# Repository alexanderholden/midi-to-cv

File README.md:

# MIDI to CV converter
This is a project that will allow me to read MIDI commands from my computer and then play my analogue synthesisers with it.

This is the first version and it features a 1V/Oct output and a gate output.

## Future upgrades:
- More features (CC and velocity for example)
- Upgrade to USB-C
- Redesign PCB to be more efficient and not require an entire Raspberry Pi Pico

## Current status:
- PCB ordered
- Custom firmware in development

## Rendering:

## Schematic:

## Parts list:

- Raspberry Pi Pico 2020
- MCP4725 12-bit DAC
- 2x 2K resistors
- 3x 10K resistors
- Polulu 5V step up converter
- 2x 1/4 audio jack

## Sources:

- MCP4725 breakout board schematic: https://learn.adafruit.com/mcp4725-12-bit-dac-tutorial/download
- QtPy MIDI to CV Skull: https://learn.adafruit.com/circuitpython-midi-to-cv-skull
- MIDI info: https://www.instructables.com/Send-and-Receive-MIDI-with-Arduino/
- Arduino MIDI to CV: https://www.instructables.com/Another-MIDI-to-CV-Box-/

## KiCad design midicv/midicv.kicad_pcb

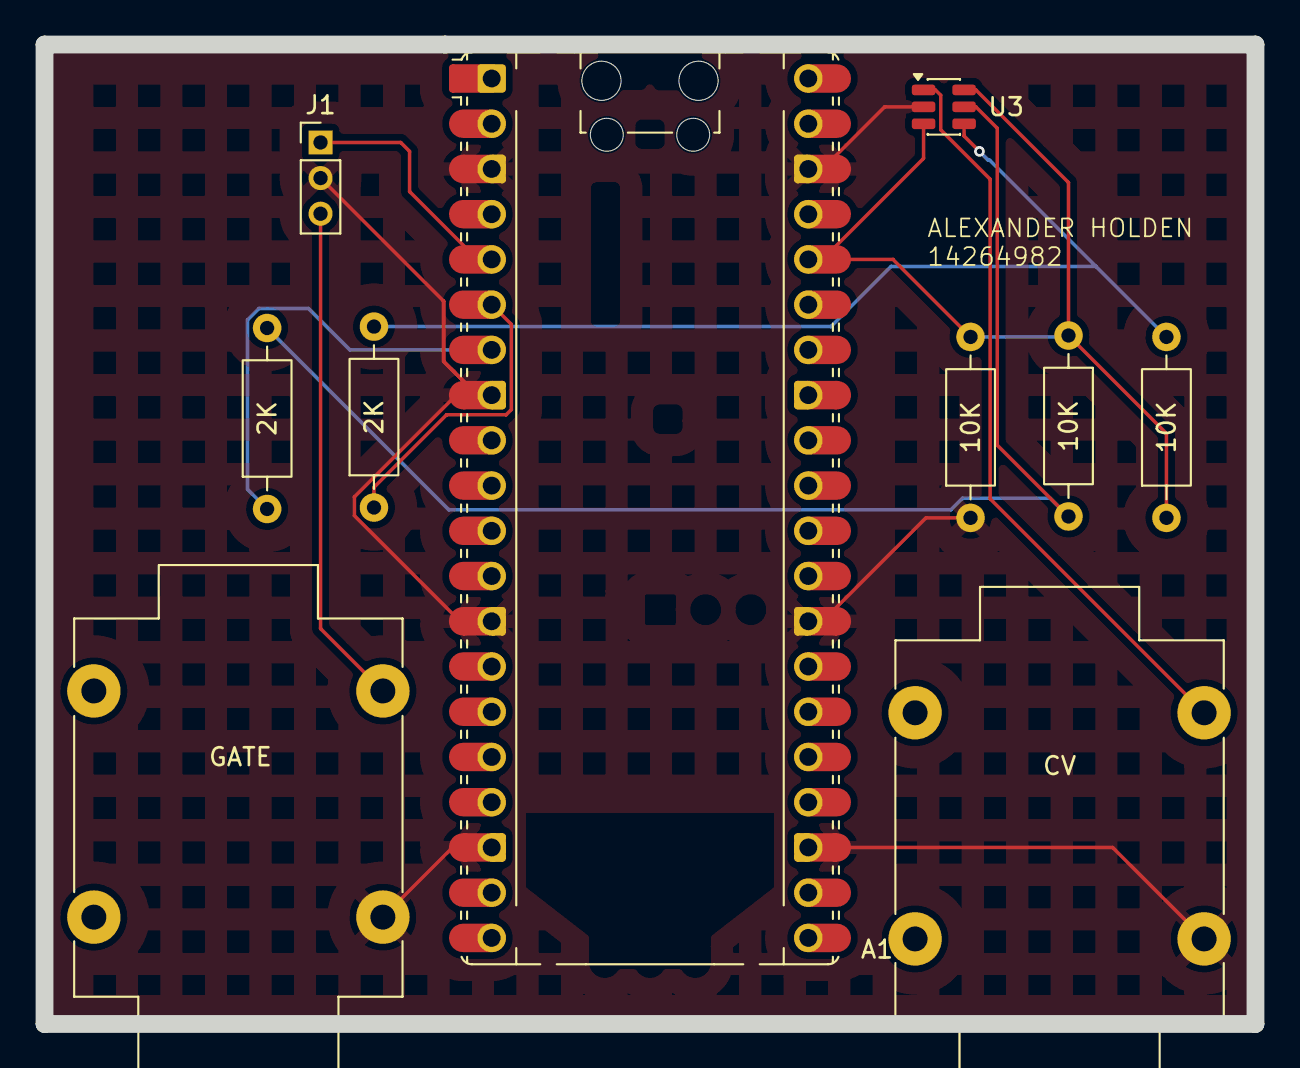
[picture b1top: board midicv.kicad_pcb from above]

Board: 2 copper layers, 68.0 x 55.0 mm, 10 parts (0 on the bottom side), 9 nets.

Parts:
2K, 2K#2: 2K; R_Axial_DIN0207_L6.3mm_D2.5mm_P10.16mm_Horizontal
10K, 10K#2, 10K#3: 10K; R_Axial_DIN0207_L6.3mm_D2.5mm_P10.16mm_Horizontal
A1: RaspberryPi_Pico; RaspberryPi_Pico_Common_Unspecified
CV: AudioJack2; Jack_6.35mm_Neutrik_NMJ4HFD2_Horizontal
GATE: AudioJack2; Jack_6.35mm_Neutrik_NMJ4HFD2_Horizontal
J1: Conn_01x03; PinHeader_1x03_P2.00mm_Vertical
U3: MCP4725xxx-xCH; SOT-23-6

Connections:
+3V3: 10K.2, 10K#2.1, 10K#3.1, A1.36 (3V3), U3.3 (VDD), U3.6 (A0)
GND: 10K.1, A1.3 (GND), A1.8 (GND), A1.13 (GND), A1.18 (GND), A1.23 (GND), A1.28 (GND), A1.38 (GND), CV.S, GATE.S, J1.2, U3.2 (VSS)
unnamed: A1.5 (GPIO3), J1.1
unnamed: 2K.1, A1.6 (GPIO4)
unnamed: 2K#2.1, A1.7 (GPIO5)
unnamed: GATE.T, J1.3
unnamed: 2K#2.2, 10K#2.2, U3.5 (SCL)
unnamed: 2K.2, 10K#3.2, U3.4 (SDA)
unnamed: CV.T, U3.1 (VOUT)
